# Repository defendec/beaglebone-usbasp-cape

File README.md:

Cape for BeagleBone that can be used for programming and logging AVR devices using usbasp connector.

# Known issues
Revision A uses pins that are used by BeagleBone emmc interface. Therefore following cut and paste changes must be made:

    P8 B23 -> P8 B19 [GPIO0_22]
    P8 B25 -> P8 B26 [GPIO1_29]
    P8 B5  -> P8 B7  [GPIO2_2 ]
    
MISO and MOSI pins are swapped, it can be corrected on software side.
TODO: how to do it.

# License
This work is licensed under CC BY-SA 3.0 http://creativecommons.org/licenses/by-sa/3.0/

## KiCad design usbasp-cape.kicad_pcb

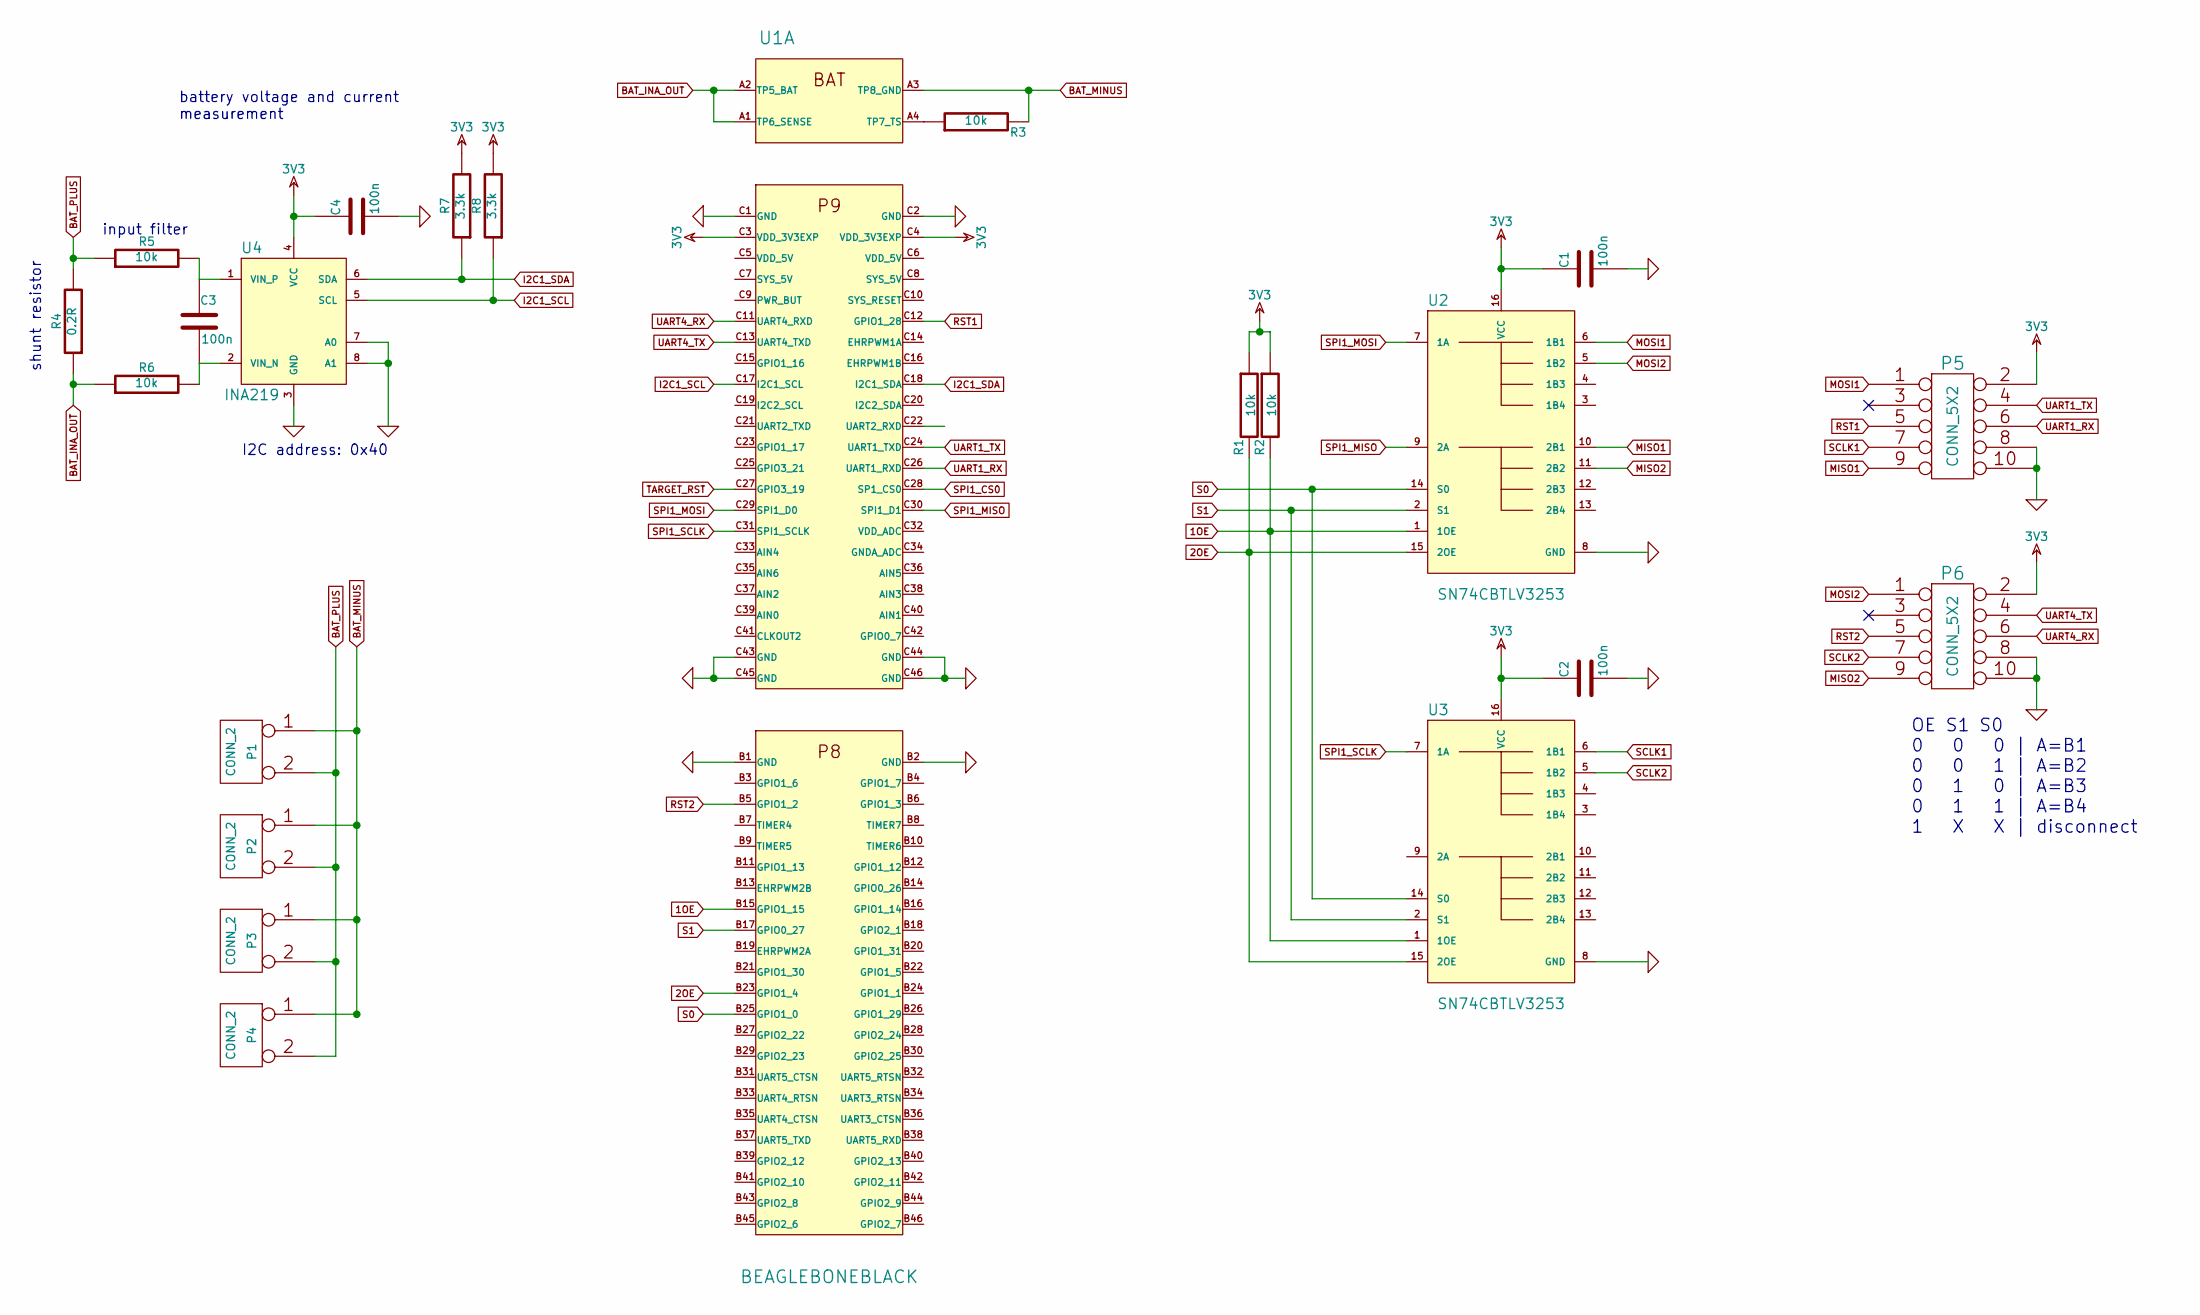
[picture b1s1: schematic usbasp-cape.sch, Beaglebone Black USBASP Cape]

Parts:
C1, C2, C3, C4: 100n
P1, P2, P3, P4: CONN_2
P5, P6: CONN_5X2; Farnell 1022236
R1, R2, R3, R5, R6: 10k
R4: 0.2R
R7, R8: 3.3k
U1: BEAGLEBONEBLACK
U2, U3: SN74CBTLV3253; Farnell 1752922
U4: INA219; Farnell 2295989

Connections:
1OE: R2.2, U1.B15 (GPIO1_15), U2.1 (1OE), U3.1 (1OE)
2OE: R1.2, U1.B23 (GPIO1_4), U2.15 (2OE), U3.15 (2OE)
3V3: C1.1, C2.1, C4.1, P5.2, P6.2, R1.1, R2.1, R7.2, R8.2, U1.C3 (VDD_3V3EXP), U1.C4 (VDD_3V3EXP), U2.16 (VCC), U3.16 (VCC), U4.4 (VCC)
BAT_INA_OUT: R4.1, R6.1, U1.A1 (TP6_SENSE), U1.A2 (TP5_BAT)
BAT_MINUS: P1.1, P2.1, P3.1, P4.1, R3.2, U1.A3 (TP8_GND)
BAT_PLUS: P1.2 (PM), P2.2 (PM), P3.2 (PM), P4.2 (PM), R4.2, R5.1
GND: C1.2, C2.2, C4.2, P5.8, P5.10, P6.8, P6.10, U1.B1 (GND), U1.B2 (GND), U1.C1 (GND), U1.C2 (GND), U1.C43 (GND), U1.C44 (GND), U1.C45 (GND), U1.C46 (GND), U1.M1, U1.M2, U1.M3, U1.M4, U2.8 (GND), U3.8 (GND), U4.3 (GND), U4.7 (A0), U4.8 (A1)
I2C1_SCL: R8.1, U1.C17 (I2C1_SCL), U4.5 (SCL)
I2C1_SDA: R7.1, U1.C18 (I2C1_SDA), U4.6 (SDA)
MISO1: P5.9, U2.10 (2B1)
MISO2: P6.9, U2.11 (2B2)
MOSI1: P5.1, U2.6 (1B1)
MOSI2: P6.1, U2.5 (1B2)
unnamed: R3.1, U1.A4 (TP7_TS)
unnamed: C3.2, R6.2, U4.2 (VIN_N)
unnamed: C3.1, R5.2, U4.1 (VIN_P)
RST1: P5.5, U1.C12 (GPIO1_28)
RST2: P6.5, U1.B5 (GPIO1_2)
S0: U1.B25 (GPIO1_0), U2.14 (S0), U3.14 (S0)
S1: U1.B17 (GPIO0_27), U2.2 (S1), U3.2 (S1)
SCLK1: P5.7, U3.6 (1B1)
SCLK2: P6.7, U3.5 (1B2)
SPI1_CS0: U1.C28 (SP1_CS0)
SPI1_MISO: U1.C30 (SPI1_D1), U2.9 (2A)
SPI1_MOSI: U1.C29 (SPI1_D0), U2.7 (1A)
SPI1_SCLK: U1.C31 (SPI1_SCLK), U3.7 (1A)
TARGET_RST: U1.C27 (GPIO3_19)
UART1_RX: P5.6, U1.C26 (UART1_RXD)
UART1_TX: P5.4, U1.C24 (UART1_TXD)
UART4_RX: P6.6, U1.C11 (UART4_RXD)
UART4_TX: P6.4, U1.C13 (UART4_TXD)

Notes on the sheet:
OE S1 S0 0 0 0 | A=B1 0 0 1 | A=B2 0 1 0 | A=B3 0 1 1 | A=B4 1 X X | disconnect
shunt resistor
input filter
battery voltage and current measurement
I2C address: 0x40

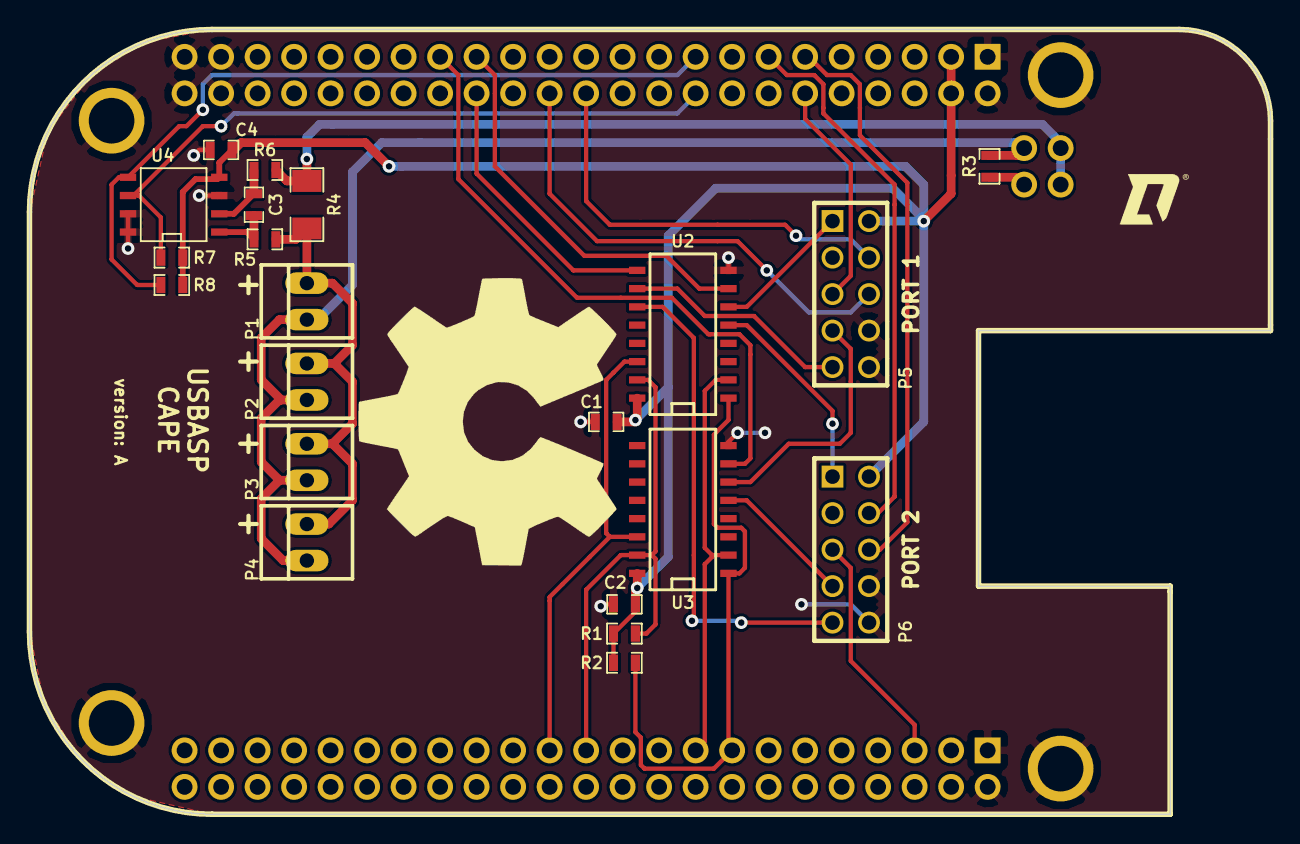
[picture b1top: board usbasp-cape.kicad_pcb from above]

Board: 2 copper layers, 86.4 x 54.6 mm, 23 parts (0 on the bottom side), 29 nets.

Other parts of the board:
VAL: REF; logo_d_tag

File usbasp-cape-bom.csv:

Reference,Value,LibPart,Footprint,Qty,Farnell
"C1, C2, C3, C4",100n,device:C,,4,
"P1, P2, P3, P4",CONN_2,conn:CONN_2,,4,
"P5, P6",CONN_5X2,conn:CONN_5X2,,2,1022236
"R1, R2, R3, R5, R6",10k,device:R,,5,
R4,0.2R,device:R,,1,
"R7, R8",3.3k,device:R,,2,
U1,BEAGLEBONEBLACK,beagleboneblack:BEAGLEBONEBLACK,,1,
"U2, U3",SN74CBTLV3253,defendec:SN74CBTLV3253,,2,1752922
U4,INA219,defendec:INA219,,1,2295989

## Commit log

2014-08-30 initial clean cape version
    add beagle bone libs
2014-08-31 add SN74CBTLV3235 1:4 mux to defendeC lib
2014-08-31 update beaglebone black battery connector symbol
2014-08-31 add mux and connectors to schematic
2014-09-01 add INA219 to defendec.lib
2014-09-01 add INA219 to schematic
2014-09-01 rewire some io pins for better routing
2014-09-01 pcb board routed, silkscreen not ready
2014-09-01 add oshw and d-tag to defendec.mod
2014-09-01 add logos to silkscreen, add polygons
2014-09-02 add BOM
2014-09-02 connect mounting holes to GND
2014-09-02 add gerber files
2014-09-02 add pdf schematic
2014-09-02 save .pro
2014-09-02 reworked ground fills
2014-09-02 generate gerbers with reworked copper fills
2014-09-16 License as CC BY-SA 3.0
2014-09-16 Add license to readme
2014-10-14 Add revision A fixes to readme
2014-11-20 Add more workarounds to README
2014-12-08 Add bbb debian configuration ansible scripts
2014-12-09 Fix some pin conf and add a big readme.
2015-01-15 debian-install readme updates and autossh verbosity tunedown
2015-01-21 updade deploy scripts
2015-01-22 fix printf-uart-nanomsg systemd startup file
2015-01-23 removing logging-tools from git history
2015-01-23 rm logging-tools from .gitignore
2015-01-23 change path in printf-uart-nanomsg@.service
